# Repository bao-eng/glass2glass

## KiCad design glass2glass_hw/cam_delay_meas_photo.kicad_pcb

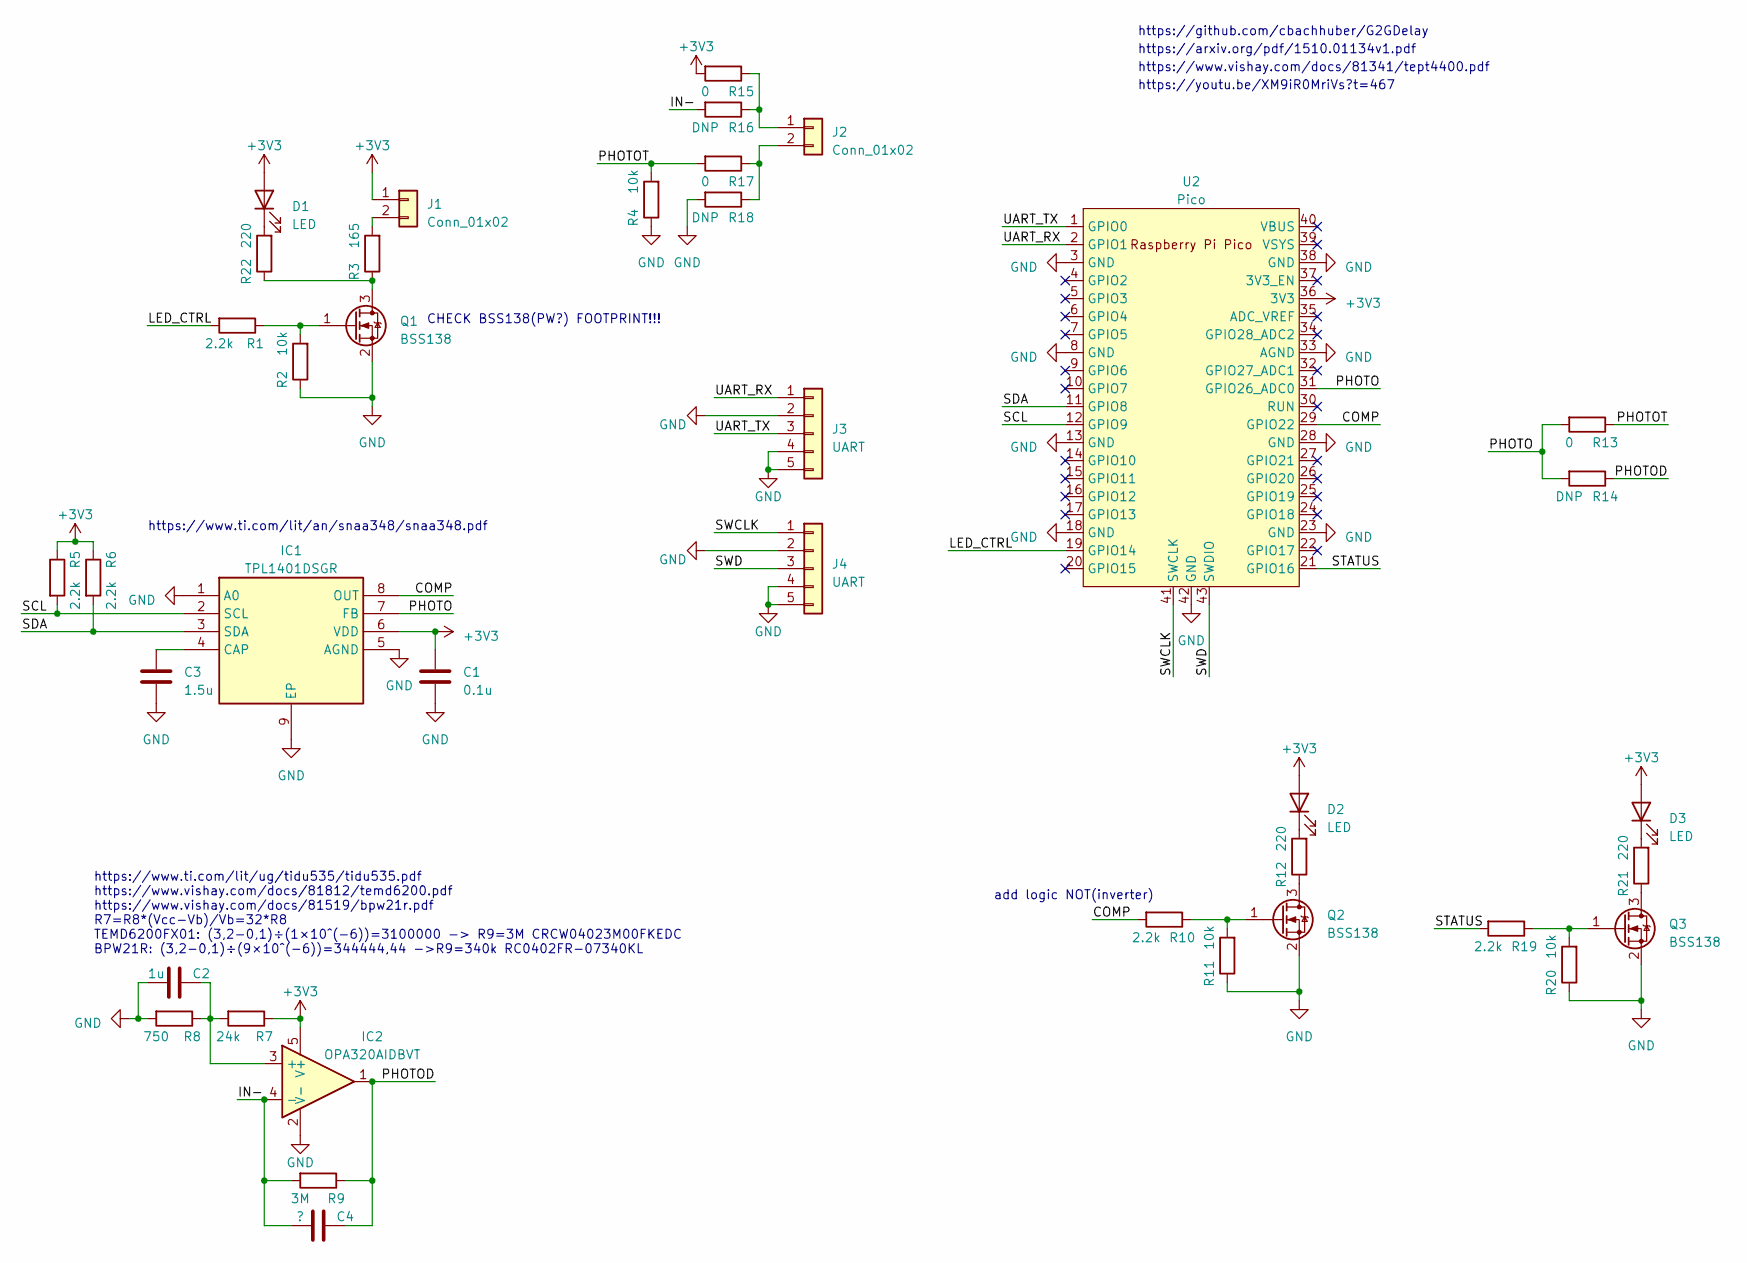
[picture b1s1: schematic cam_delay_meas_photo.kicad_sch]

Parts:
C1: 0.1u; C_0805_2012Metric; MPN CC0805KRX7R9BB104
C2: 1u; C_0402_1005Metric; MPN CC0402KRX5R5BB105
C3: 1.5u; C_0805_2012Metric; MPN CC0805ZRY5V7BB155
C4: ?; C_0402_1005Metric
D1: LED; LED_0603_1608Metric; MPN LTST-C191KFKT
D2: LED; LED_0603_1608Metric; MPN LTST-C191TBKT
D3: LED; LED_0603_1608Metric; MPN LTST-C191KGKT
IC1: TPL1401DSGR; SON50P200X200X80-9N; Mouser Part Number 595-TPL1401DSGR
IC2: OPA320AIDBVT; SOT95P280X145-5N; Mouser Part Number 595-OPA320AIDBVT
J1, J2: Conn_01x02; SHDRRA2W80P0X350_1X2_840X920X720P
J3, J4: UART; CONN_SM03B-SRSS-TB_JST; MPN SM03B-SRSS-TB(LF)(SN)
Q1, Q2, Q3: BSS138; SOT-323_SC-70; MPN BSS138PW
R1, R6, R10, R19: 2.2k; R_0402_1005Metric
R2, R11, R20: 10k; R_0402_1005Metric; MPN RC0402FR-0710KL
R3: 165; R_0805_2012Metric; MPN RC0805FR-07165RL
R4: 10k; R_0805_2012Metric; MPN RC0805FR-0710KL
R5: 2.2k; R_0402_1005Metric; MPN RC0402FR-072K2L
R7: 24k; R_0402_1005Metric; MPN RC0402FR-0724KL
R8: 750; R_0402_1005Metric; MPN RC0402FR-07750RL
R9: 3M; R_0402_1005Metric; MPN CRCW04023M00FKEDC
R12, R21, R22: 220; R_0402_1005Metric; MPN RC0402FR-07220RL
R13, R15, R17: 0; R_0402_1005Metric; MPN RC0402JR-070RL
R14, R16, R18: DNP; R_0402_1005Metric
U2: Pico; RPi_Pico_SMD

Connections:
+3V3: C1.1, D1.2 (A), D2.2 (A), D3.2 (A), IC1.6 (VDD), IC2.5 (V+), J1.1, R5.1, R6.1, R7.1, R15.2, U2.36 (3V3)
/COMP: IC1.8 (OUT), R10.2, U2.29 (GPIO22)
/IN-: C4.1, IC2.4 (-), R9.2, R16.2
/LED_CTRL: R1.2, U2.19 (GPIO14)
/PHOTO: IC1.7 (FB), R13.2, R14.2, U2.31 (GPIO26_ADC0)
/PHOTOD: C4.2, IC2.1, R9.1, R14.1
/PHOTOT: R4.2, R13.1, R17.2
/SCL: IC1.2 (SCL), R5.2, U2.12 (GPIO9)
/SDA: IC1.3 (SDA), R6.2, U2.11 (GPIO8)
/STATUS: R19.2, U2.21 (GPIO16)
/SWCLK: J4.1, U2.41 (SWCLK)
/SWD: J4.3, U2.43 (SWDIO)
/UART_RX: J3.1, U2.2 (GPIO1)
/UART_TX: J3.3, U2.1 (GPIO0)
GND: C1.2, C2.1, C3.2, IC1.1 (A0), IC1.5 (AGND), IC1.9 (EP), IC2.2 (V-), J3.2, J3.4, J3.5, J4.2, J4.4, J4.5, Q1.2 (S), Q2.2 (S), Q3.2 (S), R2.1, R4.1, R8.2, R11.1, R18.2, R20.1, U2.3 (GND), U2.8 (GND), U2.13 (GND), U2.18 (GND), U2.23 (GND), U2.28 (GND), U2.33 (AGND), U2.38 (GND), U2.42 (GND)
unnamed: D1.1 (K), R22.2
unnamed: D2.1 (K), R12.2
unnamed: D3.1 (K), R21.2
unnamed: C3.1, IC1.4 (CAP)
unnamed: C2.2, IC2.3 (+), R7.2, R8.1
unnamed: J1.2, R3.2
unnamed: J2.1, R15.1, R16.1
unnamed: J2.2, R17.1, R18.1
unnamed: Q1.3 (D), R3.1, R22.1
unnamed: Q1.1 (G), R1.1, R2.2
unnamed: Q2.3 (D), R12.1
unnamed: Q2.1 (G), R10.1, R11.2
unnamed: Q3.3 (D), R21.1
unnamed: Q3.1 (G), R19.1, R20.2

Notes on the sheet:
https://www.ti.com/lit/an/snaa348/snaa348.pdf
add logic NOT(inverter)
https://www.vishay.com/docs/81341/tept4400.pdf
https://youtu.be/XM9iR0MriVs?t=467
https://www.ti.com/lit/ug/tidu535/tidu535.pdf https://www.vishay.com/docs/81812/temd6200.pdf https://www.vishay.com/docs/81519/bpw21r.pdf R7=R8*(Vcc-Vb)/Vb=32*R8 TEMD6200FX01: (3,2−0,1)÷(1×10^(−6))=3100000 -> R9=3M CRCW04023M00FKEDC BPW21R: (3,2−0,1)÷(9×10^(−6))=344444,44 ->R9=340k RC0402FR-07340KL
https://github.com/cbachhuber/G2GDelay
https://arxiv.org/pdf/1510.01134v1.pdf
CHECK BSS138(PW?) FOOTPRINT!!!

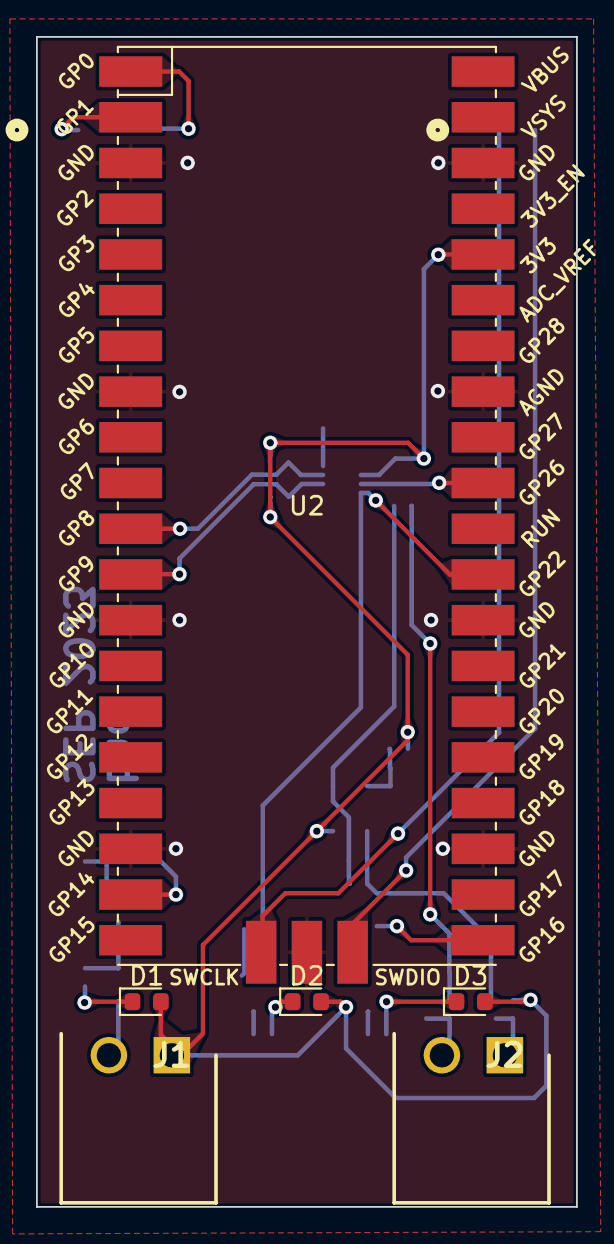
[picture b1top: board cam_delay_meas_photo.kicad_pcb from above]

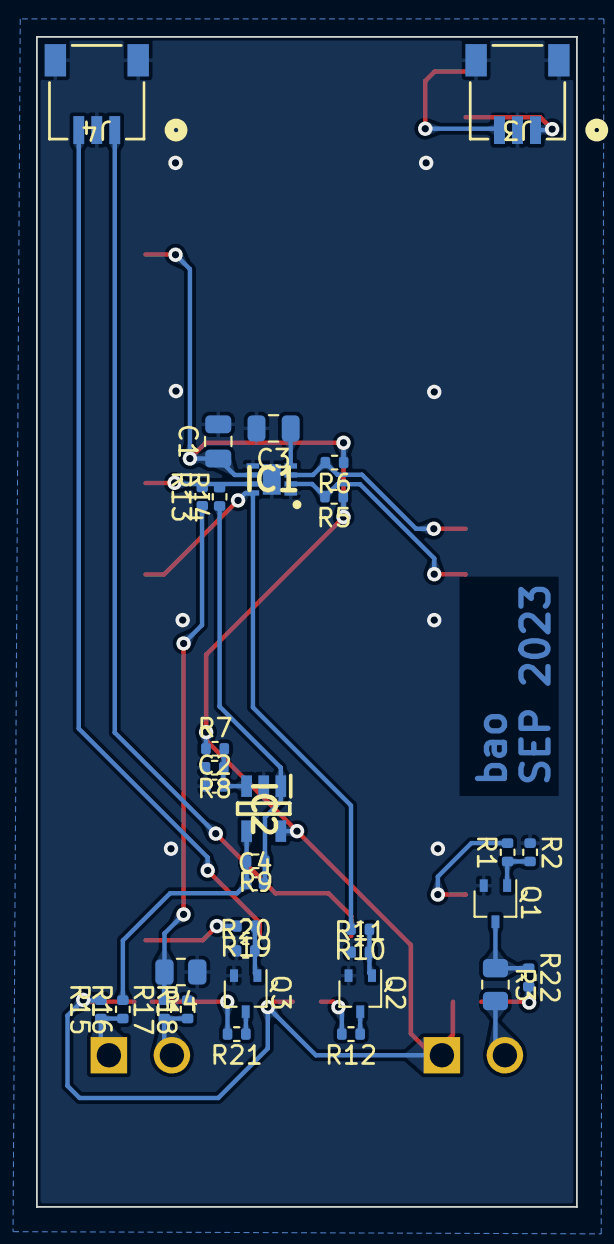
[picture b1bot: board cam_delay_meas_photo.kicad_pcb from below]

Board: 2 copper layers, 30.0 x 65.0 mm, 39 parts (33 on the bottom side), 29 nets.

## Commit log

2023-09-16 FETs fixed + added inverter
2023-09-23 tpl1401 driver added
2023-09-23 move sources to the root dir
2023-09-23 remove hw files(moved to the separate repo)
2023-09-23 remove redundant delay
2023-09-23 tpl1401_reg_read regaddr argument fixed
2023-09-23 repeating timer added
2023-09-28 use argument i2c instance of default
2023-09-30 Status LED added
2023-09-30 pass data via pointers
2023-09-30 gpio interrupt added
2023-09-30 glass to glass delay measurement
